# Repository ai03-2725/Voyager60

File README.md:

# Voyager60-Alps
A fully featured Alps-specific 60% PCB

#### In light of recent claims that I am 100% liable for any of my open source PCBs, I am adding this disclaimer.
#### I provide these PCBs as a reference for designing keyboard PCBs. Using them within your projects will require a will to do research of one's own and to learn the workings of them, potentially fixing issues if they exist.
# I provide these PCBs without liability and without any guarantees regarding functionality, as expressed in the MIT license under which all of these PCBs are licensed.

### Features
* RGB underglow
* Decent amount of layout compatibility - [View supported layouts](http://www.keyboard-layout-editor.com/#/gists/c867bdba7e5ae8be282f77a242bacf66)
* Slot cutout for maximum flexibility and typing comfort
* Over-current and static discharge protection
* Fully open-source

### Credits
This project borrows some of the compatible layouts from [Hasu's Alps64](https://github.com/tmk/alps64), especially regarding ISO compatibility positions.

### The Voyager PCB Family
The Voyager PCBs offer fully featured PCBs fit for any keyboard, whether mass production or high-end.

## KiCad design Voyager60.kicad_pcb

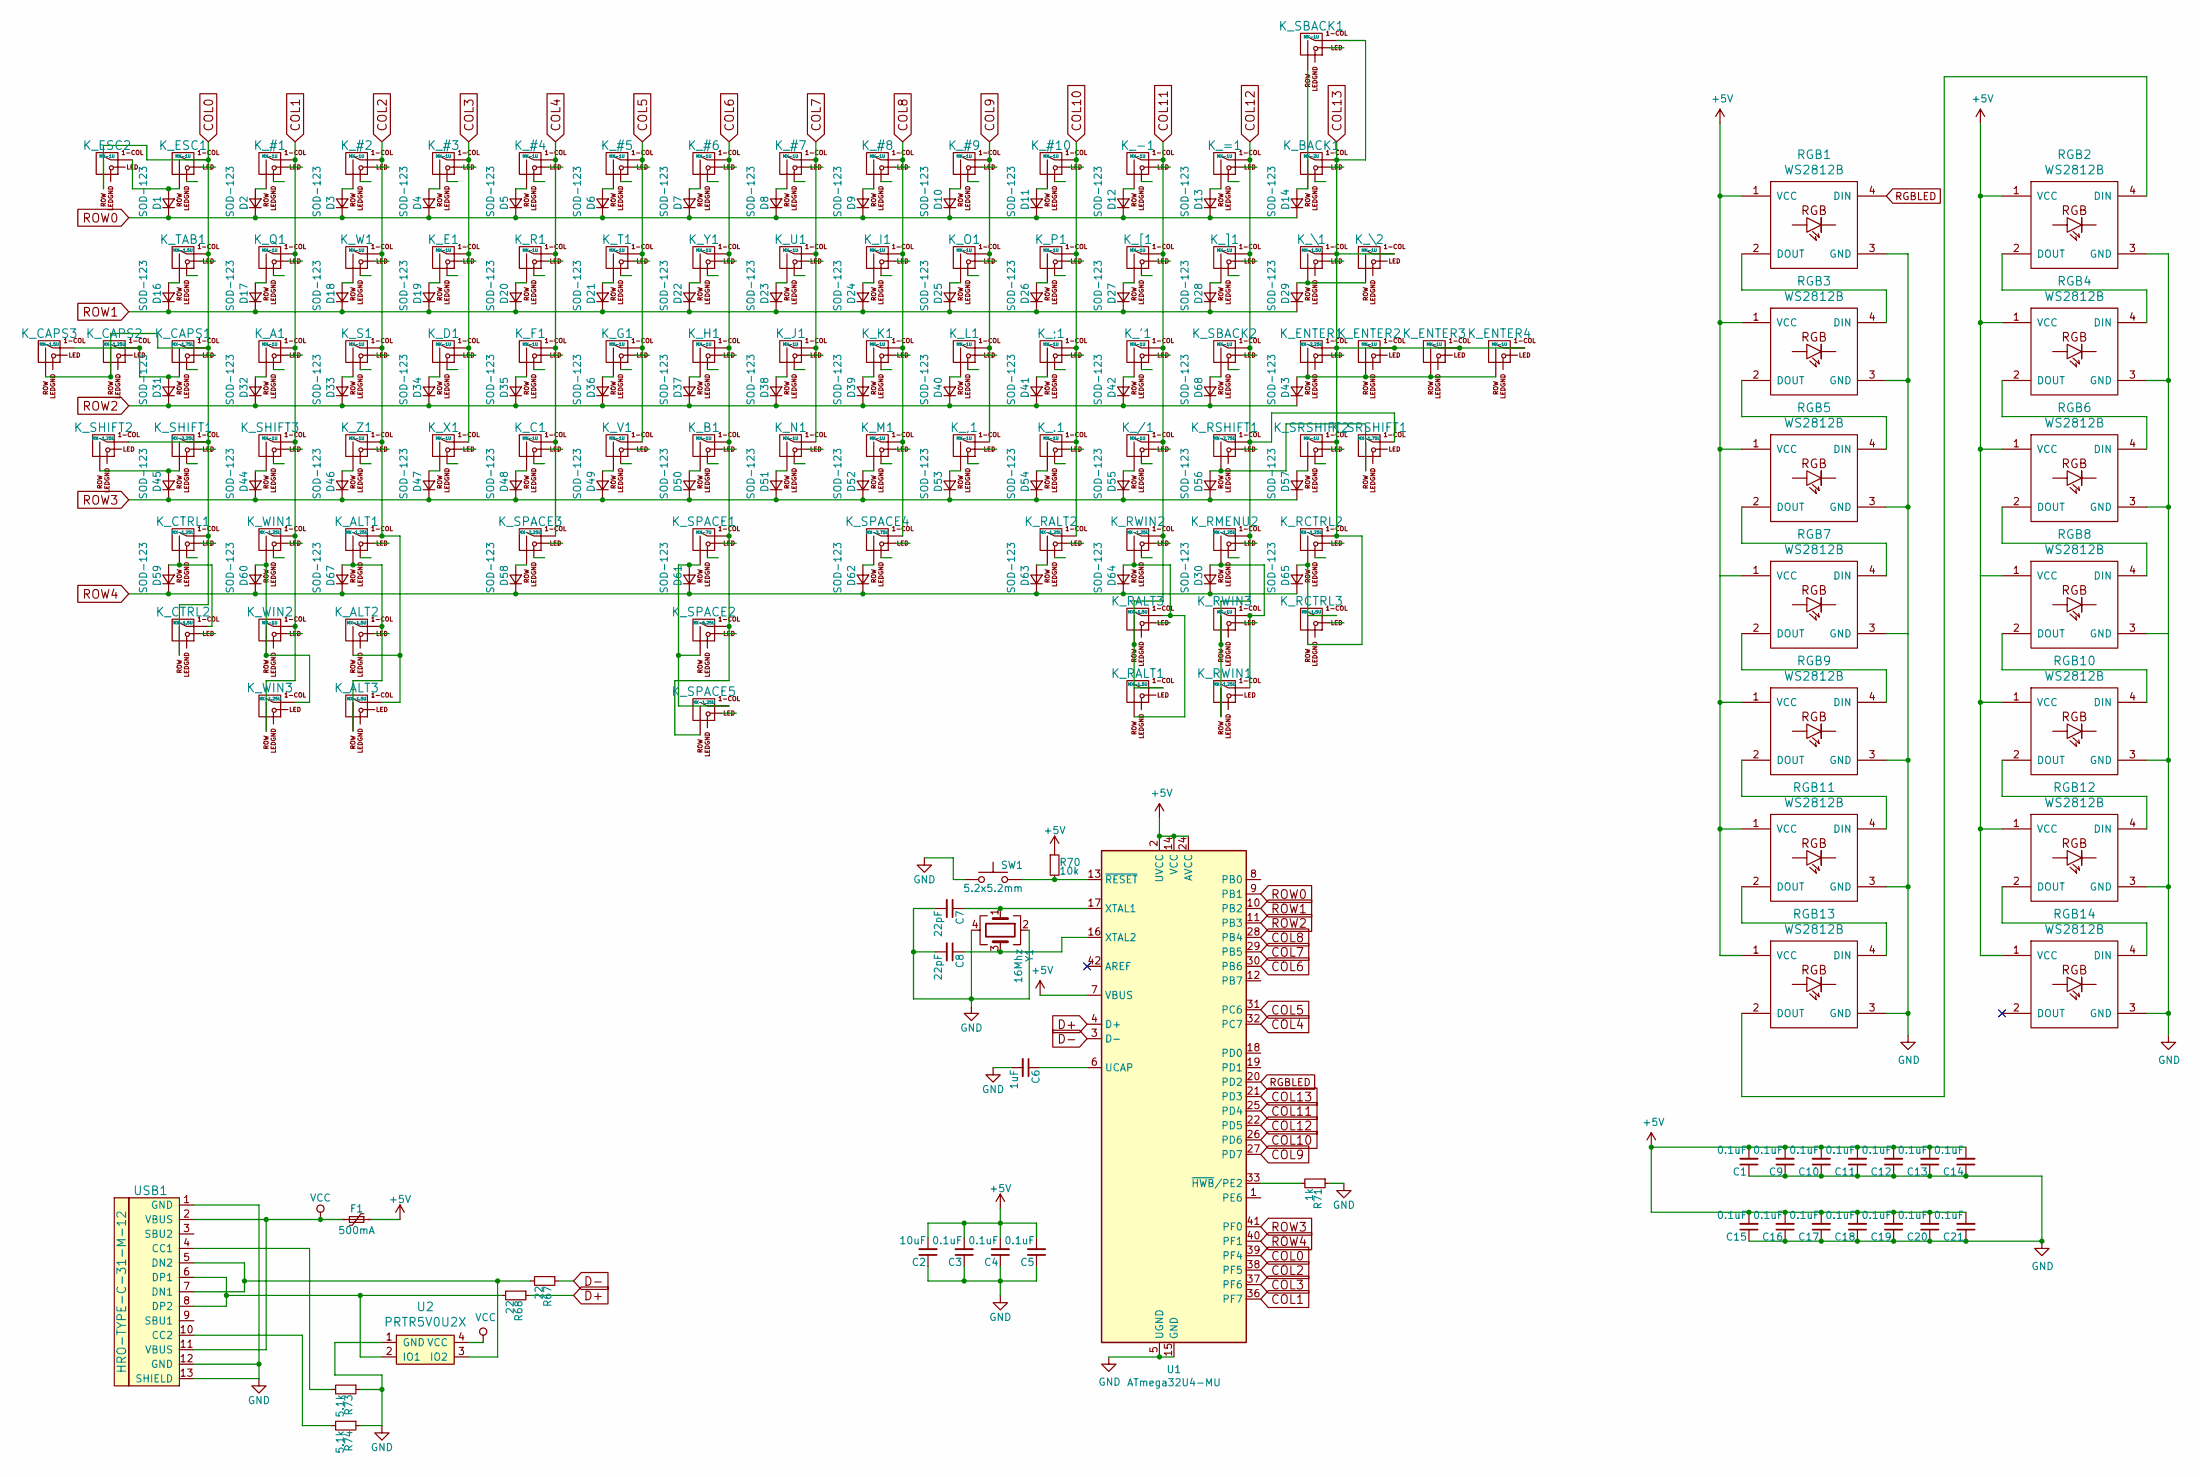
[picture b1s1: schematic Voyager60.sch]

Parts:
C1, C3, C4, C5, C9, C10, C11, C12, C13, C14, C15, C16, C17, C18, C19, C20, C21: 0.1uF; C_0603
C2: 10uF; C_0603
C6: 1uF; C_0603
C7, C8: 22pF; C_0603
D1, D2, D3, D4, D5, D6, D7, D8, D9, D10, D11, D12, D13, D14, D16, D17, D18, D19, D20, D21, D22, D23, D24, D25, D26, D27, D28, D29, D30, D31, D32, D33, D34, D35, D36, D37, D38, D39, D40, D41, D42, D43, D44, D45, D46, D47, D48, D49, D50, D51, D52, D53, D54, D55, D56, D57, D58, D59, D60, D61, D62, D63, D64, D65, D67, D68: SOD-123; D_SOD-123
F1: 500mA; Fuse_SMD1206_Reflow
K_#1, K_#2, K_#3, K_#4, K_#5, K_#6, K_#7, K_#8, K_#9, K_#10: MX-1U; ALPS-1U
K_'1: MX-1U; ALPS-1U
K_,1: MX-1U; ALPS-1U
K_-1: MX-1U; ALPS-1U
K_.1: MX-1U; ALPS-1U
K_/1: MX-1U; ALPS-1U
K_;1: MX-1U; ALPS-1U
K_=1: MX-1U; ALPS-1U
K_A1: MX-1U; ALPS-1U
K_ALT1: MX-1.25U; ALPS-1.25U
K_ALT2, K_ALT3: MX-1.5U; ALPS-1.5U
K_B1: MX-1U; ALPS-1U
K_BACK1: MX-2U; ALPS-2U
K_C1: MX-1U; ALPS-1U
K_CAPS1: MX-1.75U; ALPS-1.75U
K_CAPS2: MX-1.25U; ALPS-1.25U
K_CAPS3: MX-1.5U; ALPS-1.5U
K_CTRL1: MX-1.25U; ALPS-1.25U
K_CTRL2: MX-1.5U; ALPS-1.5U
K_D1: MX-1U; ALPS-1U
K_E1: MX-1U; ALPS-1U
K_ENTER1: MX-2.25U; ALPS-2.25U
K_ENTER2, K_ENTER3, K_ENTER4: MX-1U; ALPS-1U
K_ESC1, K_ESC2: MX-1U; ALPS-1U
K_F1: MX-1U; ALPS-1U
K_G1: MX-1U; ALPS-1U
K_H1: MX-1U; ALPS-1U
K_I1: MX-1U; ALPS-1U
K_J1: MX-1U; ALPS-1U
K_K1: MX-1U; ALPS-1U
K_L1: MX-1U; ALPS-1U
K_M1: MX-1U; ALPS-1U
K_N1: MX-1U; ALPS-1U
K_O1: MX-1U; ALPS-1U
K_P1: MX-1U; ALPS-1U
K_Q1: MX-1U; ALPS-1U
K_R1: MX-1U; ALPS-1U
K_RALT1, K_RALT3: MX-1.5U; ALPS-1.5U
K_RALT2: MX-1.25U; ALPS-1.25U
K_RCTRL2: MX-1.25U; ALPS-1.25U
K_RCTRL3: MX-1.5U; ALPS-1.5U
K_RMENU2: MX-1.25U; ALPS-1.25U
K_RSHIFT1: MX-2.75U; ALPS-2.75U
K_RWIN1, K_RWIN2: MX-1.25U; ALPS-1.25U
K_RWIN3: MX-1U; ALPS-1U
K_S1: MX-1U; ALPS-1U
K_SBACK1, K_SBACK2: MX-1U; ALPS-1U
K_SHIFT1: MX-2.25U; ALPS-2.25U
K_SHIFT2: MX-1.25U; ALPS-1.25U
K_SHIFT3: MX-1U; ALPS-1U
K_SPACE1: MX-7U; ALPS-7U
K_SPACE2: MX-6.25U; ALPS-6.25U
K_SPACE3: MX-2.25U; ALPS-2.25U
K_SPACE4: MX-2.75U; ALPS-2.75U
K_SPACE5: MX-1.25U; ALPS-1.25U
K_SRSHIFT1: MX-1.75U; ALPS-1.75U
K_SRSHIFT2: MX-1U; ALPS-1U
K_T1: MX-1U; ALPS-1U
K_TAB1: MX-1.5U; ALPS-1.5U
K_U1: MX-1U; ALPS-1U
K_V1: MX-1U; ALPS-1U
K_W1: MX-1U; ALPS-1U
K_WIN1, K_WIN3: MX-1.25U; ALPS-1.25U
K_WIN2: MX-1U; ALPS-1U
K_X1: MX-1U; ALPS-1U
K_Y1: MX-1U; ALPS-1U
K_Z1: MX-1U; ALPS-1U
K_[1: MX-1U; ALPS-1U
K_\1: MX-1.5U; ALPS-1.5U
K_\2: MX-1U; ALPS-1U
K_]1: MX-1U; ALPS-1U
R67, R68: 22; R_0805
R70: 10k; R_0805
R71: 1k; R_0805
R73, R74: 5.1k; R_0805
RGB1, RGB2, RGB3, RGB4, RGB5, RGB6, RGB7, RGB8, RGB9, RGB10, RGB11, RGB12, RGB13, RGB14: WS2812B
SW1: 5.2x5.2mm; SKQG-1155865
U1: ATmega32U4-MU; QFN-44-1EP_7x7mm_Pitch0.5mm
U2: PRTR5V0U2X; SOT143B
USB1: HRO-TYPE-C-31-M-12; HRO-TYPE-C-31-M-12-Assembly
Y1: 16Mhz; Crystal_SMD_3225-4pin_3.2x2.5mm

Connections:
+5V: C1.2, C2.2, C3.2, C4.2, C5.2, C9.2, C10.2, C11.2, C12.2, C13.2, C14.2, C15.2, C16.2, C17.2, C18.2, C19.2, C20.2, C21.2, F1.1, R70.1, RGB1.1 (VCC), RGB2.1 (VCC), RGB3.1 (VCC), RGB4.1 (VCC), RGB5.1 (VCC), RGB6.1 (VCC), RGB7.1 (VCC), RGB8.1 (VCC), RGB9.1 (VCC), RGB10.1 (VCC), RGB11.1 (VCC), RGB12.1 (VCC), RGB13.1 (VCC), RGB14.1 (VCC), U1.2 (UVCC), U1.7 (VBUS), U1.14 (VCC), U1.24 (AVCC), U1.34 (VCC), U1.44 (AVCC)
COL0: K_CAPS1.1 (COL), K_CAPS2.2 (ROW), K_CAPS3.2 (ROW), K_CTRL1.1 (COL), K_CTRL2.2 (ROW), K_ESC1.1 (COL), K_ESC2.2 (ROW), K_SHIFT1.1 (COL), K_SHIFT2.1 (COL), K_TAB1.1 (COL), U1.39 (PF4)
COL1: K_#1.1 (COL), K_A1.1 (COL), K_Q1.1 (COL), K_SHIFT3.1 (COL), K_WIN1.1 (COL), K_WIN2.1 (COL), K_WIN3.2 (ROW), U1.36 (PF7)
COL2: K_#2.1 (COL), K_ALT1.1 (COL), K_ALT2.2 (ROW), K_ALT3.1 (COL), K_S1.1 (COL), K_W1.1 (COL), K_Z1.1 (COL), U1.38 (PF5)
COL3: K_#3.1 (COL), K_D1.1 (COL), K_E1.1 (COL), K_X1.1 (COL), U1.37 (PF6)
COL4: K_#4.1 (COL), K_C1.1 (COL), K_F1.1 (COL), K_R1.1 (COL), K_SPACE3.1 (COL), U1.32 (PC7)
COL5: K_#5.1 (COL), K_G1.1 (COL), K_T1.1 (COL), K_V1.1 (COL), U1.31 (PC6)
COL6: K_#6.1 (COL), K_B1.1 (COL), K_H1.1 (COL), K_SPACE1.1 (COL), K_SPACE2.1 (COL), K_SPACE5.2 (ROW), K_Y1.1 (COL), U1.30 (PB6)
COL7: K_#7.1 (COL), K_J1.1 (COL), K_N1.1 (COL), K_U1.1 (COL), U1.29 (PB5)
COL8: K_#8.1 (COL), K_I1.1 (COL), K_K1.1 (COL), K_M1.1 (COL), K_SPACE4.1 (COL), U1.28 (PB4)
COL9: K_#9.1 (COL), K_,1.1 (COL), K_L1.1 (COL), K_O1.1 (COL), U1.27 (PD7)
COL10: K_#10.1 (COL), K_.1.1 (COL), K_;1.1 (COL), K_P1.1 (COL), K_RALT2.1 (COL), U1.26 (PD6)
COL11: K_'1.1 (COL), K_-1.1 (COL), K_/1.1 (COL), K_RALT1.1 (COL), K_RALT3.2 (ROW), K_RWIN2.1 (COL), K_[1.1 (COL), U1.25 (PD4)
COL12: K_=1.1 (COL), K_RMENU2.1 (COL), K_RSHIFT1.1 (COL), K_RWIN1.2 (ROW), K_RWIN3.2 (ROW), K_SBACK2.1 (COL), K_SRSHIFT1.1 (COL), K_]1.1 (COL), U1.22 (PD5)
COL13: K_BACK1.1 (COL), K_ENTER1.1 (COL), K_ENTER2.1 (COL), K_ENTER3.1 (COL), K_ENTER4.1 (COL), K_RCTRL2.1 (COL), K_RCTRL3.2 (ROW), K_SBACK1.1 (COL), K_SRSHIFT2.1 (COL), K_\1.1 (COL), K_\2.1 (COL), U1.21 (PD3)
D+: R68.1, U1.4 (D+)
D-: R67.1, U1.3 (D-)
GND: C1.1, C2.1, C3.1, C4.1, C5.1, C6.2, C7.2, C8.2, C9.1, C10.1, C11.1, C12.1, C13.1, C14.1, C15.1, C16.1, C17.1, C18.1, C19.1, C20.1, C21.1, R71.1, R73.1, R74.1, RGB1.3 (GND), RGB2.3 (GND), RGB3.3 (GND), RGB4.3 (GND), RGB5.3 (GND), RGB6.3 (GND), RGB7.3 (GND), RGB8.3 (GND), RGB9.3 (GND), RGB10.3 (GND), RGB11.3 (GND), RGB12.3 (GND), RGB13.3 (GND), RGB14.3 (GND), SW1.1, U1.5 (UGND), U1.15 (GND), U1.23 (GND), U1.35 (GND), U1.43 (GND), U1.45 (GND), U2.1 (GND), USB1.1 (GND), USB1.12 (GND), USB1.13 (SHIELD), Y1.2, Y1.4
unnamed: C6.1, U1.6 (UCAP)
unnamed: C7.1, U1.17 (XTAL1), Y1.1
unnamed: C8.1, U1.16 (XTAL2), Y1.3
unnamed: D1.2 (A), K_ESC1.2 (ROW), K_ESC2.1 (COL)
unnamed: D2.2 (A), K_#1.2 (ROW)
unnamed: D3.2 (A), K_#2.2 (ROW)
unnamed: D4.2 (A), K_#3.2 (ROW)
unnamed: D5.2 (A), K_#4.2 (ROW)
unnamed: D6.2 (A), K_#5.2 (ROW)
unnamed: D7.2 (A), K_#6.2 (ROW)
unnamed: D8.2 (A), K_#7.2 (ROW)
unnamed: D9.2 (A), K_#8.2 (ROW)
unnamed: D10.2 (A), K_#9.2 (ROW)
unnamed: D11.2 (A), K_#10.2 (ROW)
unnamed: D12.2 (A), K_-1.2 (ROW)
unnamed: D13.2 (A), K_=1.2 (ROW)
unnamed: D14.2 (A), K_BACK1.2 (ROW), K_SBACK1.2 (ROW)
unnamed: D16.2 (A), K_TAB1.2 (ROW)
unnamed: D17.2 (A), K_Q1.2 (ROW)
unnamed: D18.2 (A), K_W1.2 (ROW)
unnamed: D19.2 (A), K_E1.2 (ROW)
unnamed: D20.2 (A), K_R1.2 (ROW)
unnamed: D21.2 (A), K_T1.2 (ROW)
unnamed: D22.2 (A), K_Y1.2 (ROW)
unnamed: D23.2 (A), K_U1.2 (ROW)
unnamed: D24.2 (A), K_I1.2 (ROW)
unnamed: D25.2 (A), K_O1.2 (ROW)
unnamed: D26.2 (A), K_P1.2 (ROW)
unnamed: D27.2 (A), K_[1.2 (ROW)
unnamed: D28.2 (A), K_]1.2 (ROW)
unnamed: D29.2 (A), K_\1.2 (ROW), K_\2.2 (ROW)
unnamed: D30.2 (A), K_RMENU2.2 (ROW), K_RWIN1.1 (COL), K_RWIN3.1 (COL)
unnamed: D31.2 (A), K_CAPS1.2 (ROW), K_CAPS2.1 (COL), K_CAPS3.1 (COL)
unnamed: D32.2 (A), K_A1.2 (ROW)
unnamed: D33.2 (A), K_S1.2 (ROW)
unnamed: D34.2 (A), K_D1.2 (ROW)
unnamed: D35.2 (A), K_F1.2 (ROW)
unnamed: D36.2 (A), K_G1.2 (ROW)
unnamed: D37.2 (A), K_H1.2 (ROW)
unnamed: D38.2 (A), K_J1.2 (ROW)
unnamed: D39.2 (A), K_K1.2 (ROW)
unnamed: D40.2 (A), K_L1.2 (ROW)
unnamed: D41.2 (A), K_;1.2 (ROW)
unnamed: D42.2 (A), K_'1.2 (ROW)
unnamed: D43.2 (A), K_ENTER1.2 (ROW), K_ENTER2.2 (ROW), K_ENTER3.2 (ROW), K_ENTER4.2 (ROW)
unnamed: D44.2 (A), K_SHIFT3.2 (ROW)
unnamed: D45.2 (A), K_SHIFT1.2 (ROW), K_SHIFT2.2 (ROW)
unnamed: D46.2 (A), K_Z1.2 (ROW)
unnamed: D47.2 (A), K_X1.2 (ROW)
unnamed: D48.2 (A), K_C1.2 (ROW)
unnamed: D49.2 (A), K_V1.2 (ROW)
unnamed: D50.2 (A), K_B1.2 (ROW)
unnamed: D51.2 (A), K_N1.2 (ROW)
unnamed: D52.2 (A), K_M1.2 (ROW)
unnamed: D53.2 (A), K_,1.2 (ROW)
unnamed: D54.2 (A), K_.1.2 (ROW)
unnamed: D55.2 (A), K_/1.2 (ROW)
unnamed: D56.2 (A), K_RSHIFT1.2 (ROW), K_SRSHIFT1.2 (ROW)
unnamed: D57.2 (A), K_SRSHIFT2.2 (ROW)
unnamed: D58.2 (A), K_SPACE3.2 (ROW)
unnamed: D59.2 (A), K_CTRL1.2 (ROW), K_CTRL2.1 (COL)
unnamed: D60.2 (A), K_WIN1.2 (ROW), K_WIN2.2 (ROW), K_WIN3.1 (COL)
unnamed: D61.2 (A), K_SPACE1.2 (ROW), K_SPACE2.2 (ROW), K_SPACE5.1 (COL)
unnamed: D62.2 (A), K_SPACE4.2 (ROW)
unnamed: D63.2 (A), K_RALT2.2 (ROW)
unnamed: D64.2 (A), K_RALT1.2 (ROW), K_RALT3.1 (COL), K_RWIN2.2 (ROW)
unnamed: D65.2 (A), K_RCTRL2.2 (ROW), K_RCTRL3.1 (COL)
unnamed: D67.2 (A), K_ALT1.2 (ROW), K_ALT2.1 (COL), K_ALT3.2 (ROW)
unnamed: D68.2 (A), K_SBACK2.2 (ROW)
unnamed: R67.2, U2.3 (IO2), USB1.5 (DN2), USB1.7 (DN1)
unnamed: R68.2, U2.2 (IO1), USB1.6 (DP1), USB1.8 (DP2)
unnamed: R70.2, SW1.2, U1.13 (~RESET)
unnamed: R71.2, U1.33 (~HWB~/PE2)
unnamed: R73.2, USB1.4 (CC1)
unnamed: R74.2, USB1.10 (CC2)
unnamed: RGB1.2 (DOUT), RGB3.4 (DIN)
unnamed: RGB2.2 (DOUT), RGB4.4 (DIN)
unnamed: RGB3.2 (DOUT), RGB5.4 (DIN)
unnamed: RGB4.2 (DOUT), RGB6.4 (DIN)
unnamed: RGB5.2 (DOUT), RGB7.4 (DIN)
unnamed: RGB6.2 (DOUT), RGB8.4 (DIN)
unnamed: RGB7.2 (DOUT), RGB9.4 (DIN)
unnamed: RGB10.2 (DOUT), RGB12.4 (DIN)
unnamed: RGB8.2 (DOUT), RGB10.4 (DIN)
unnamed: RGB11.2 (DOUT), RGB13.4 (DIN)
unnamed: RGB9.2 (DOUT), RGB11.4 (DIN)
unnamed: RGB12.2 (DOUT), RGB14.4 (DIN)
unnamed: RGB2.4 (DIN), RGB13.2 (DOUT)
RGBLED: RGB1.4 (DIN), U1.20 (PD2)
ROW0: D1.1 (K), D2.1 (K), D3.1 (K), D4.1 (K), D5.1 (K), D6.1 (K), D7.1 (K), D8.1 (K), D9.1 (K), D10.1 (K), D11.1 (K), D12.1 (K), D13.1 (K), D14.1 (K), U1.9 (PB1)
ROW1: D16.1 (K), D17.1 (K), D18.1 (K), D19.1 (K), D20.1 (K), D21.1 (K), D22.1 (K), D23.1 (K), D24.1 (K), D25.1 (K), D26.1 (K), D27.1 (K), D28.1 (K), D29.1 (K), U1.10 (PB2)
ROW2: D31.1 (K), D32.1 (K), D33.1 (K), D34.1 (K), D35.1 (K), D36.1 (K), D37.1 (K), D38.1 (K), D39.1 (K), D40.1 (K), D41.1 (K), D42.1 (K), D43.1 (K), D68.1 (K), U1.11 (PB3)
ROW3: D44.1 (K), D45.1 (K), D46.1 (K), D47.1 (K), D48.1 (K), D49.1 (K), D50.1 (K), D51.1 (K), D52.1 (K), D53.1 (K), D54.1 (K), D55.1 (K), D56.1 (K), D57.1 (K), U1.41 (PF0)
ROW4: D30.1 (K), D58.1 (K), D59.1 (K), D60.1 (K), D61.1 (K), D62.1 (K), D63.1 (K), D64.1 (K), D65.1 (K), D67.1 (K), U1.40 (PF1)
VCC: F1.2, U2.4 (VCC), USB1.2 (VBUS), USB1.11 (VBUS)

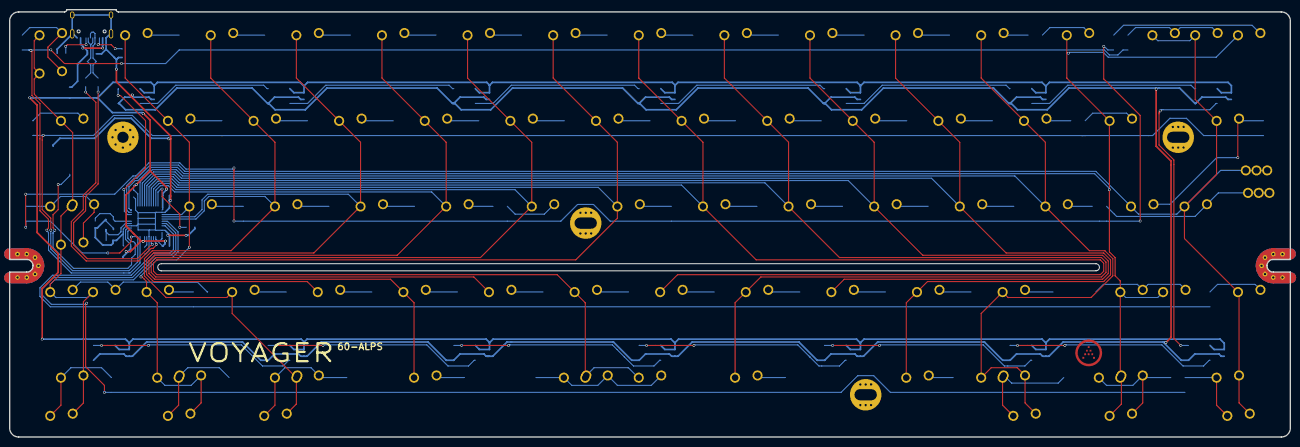
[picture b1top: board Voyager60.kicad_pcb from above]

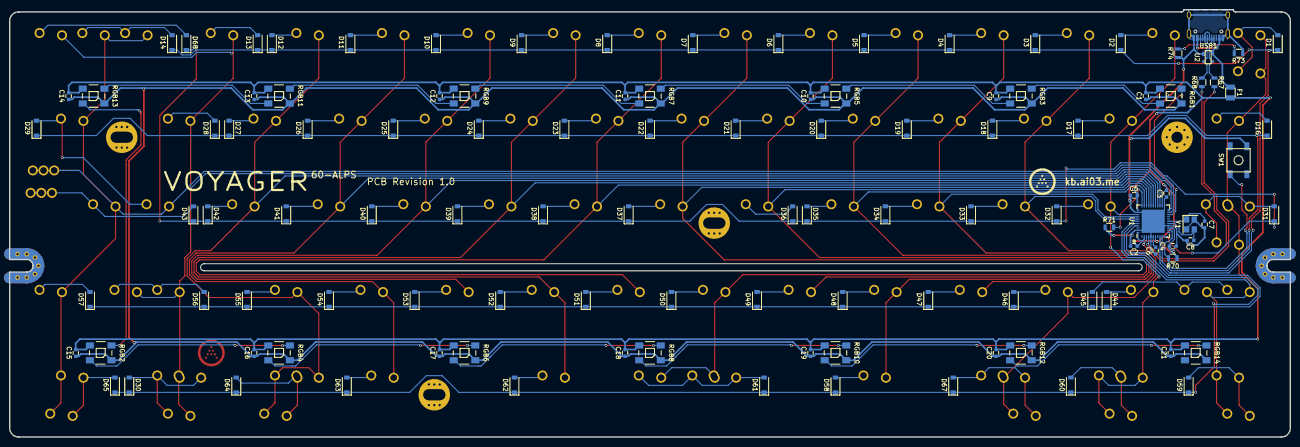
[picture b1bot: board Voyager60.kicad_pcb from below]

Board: 2 copper layers, 285.0 x 95.1 mm, 201 parts (113 on the bottom side), 113 nets.

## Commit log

2018-12-25 Add submodules
2018-12-25 Add local library files
2018-12-25 Begin progress
2018-12-25 Progress
2019-01-04 Place components
2019-01-07 Continue routing
2019-01-15 Finish routing
2019-01-15 Update Submodules
2019-01-15 Route RGBs
2019-01-15 Finish routing, add decorations
2019-01-15 Generate production data
2019-01-15 Create LICENSE
2019-01-27 Update logo to universal spec
2019-03-07 Updated MX submod
2019-03-07 Update submod
2019-03-07 Make alps variant
2019-03-07 Push changes
2019-03-07 New bom
2019-03-26 Update bom
